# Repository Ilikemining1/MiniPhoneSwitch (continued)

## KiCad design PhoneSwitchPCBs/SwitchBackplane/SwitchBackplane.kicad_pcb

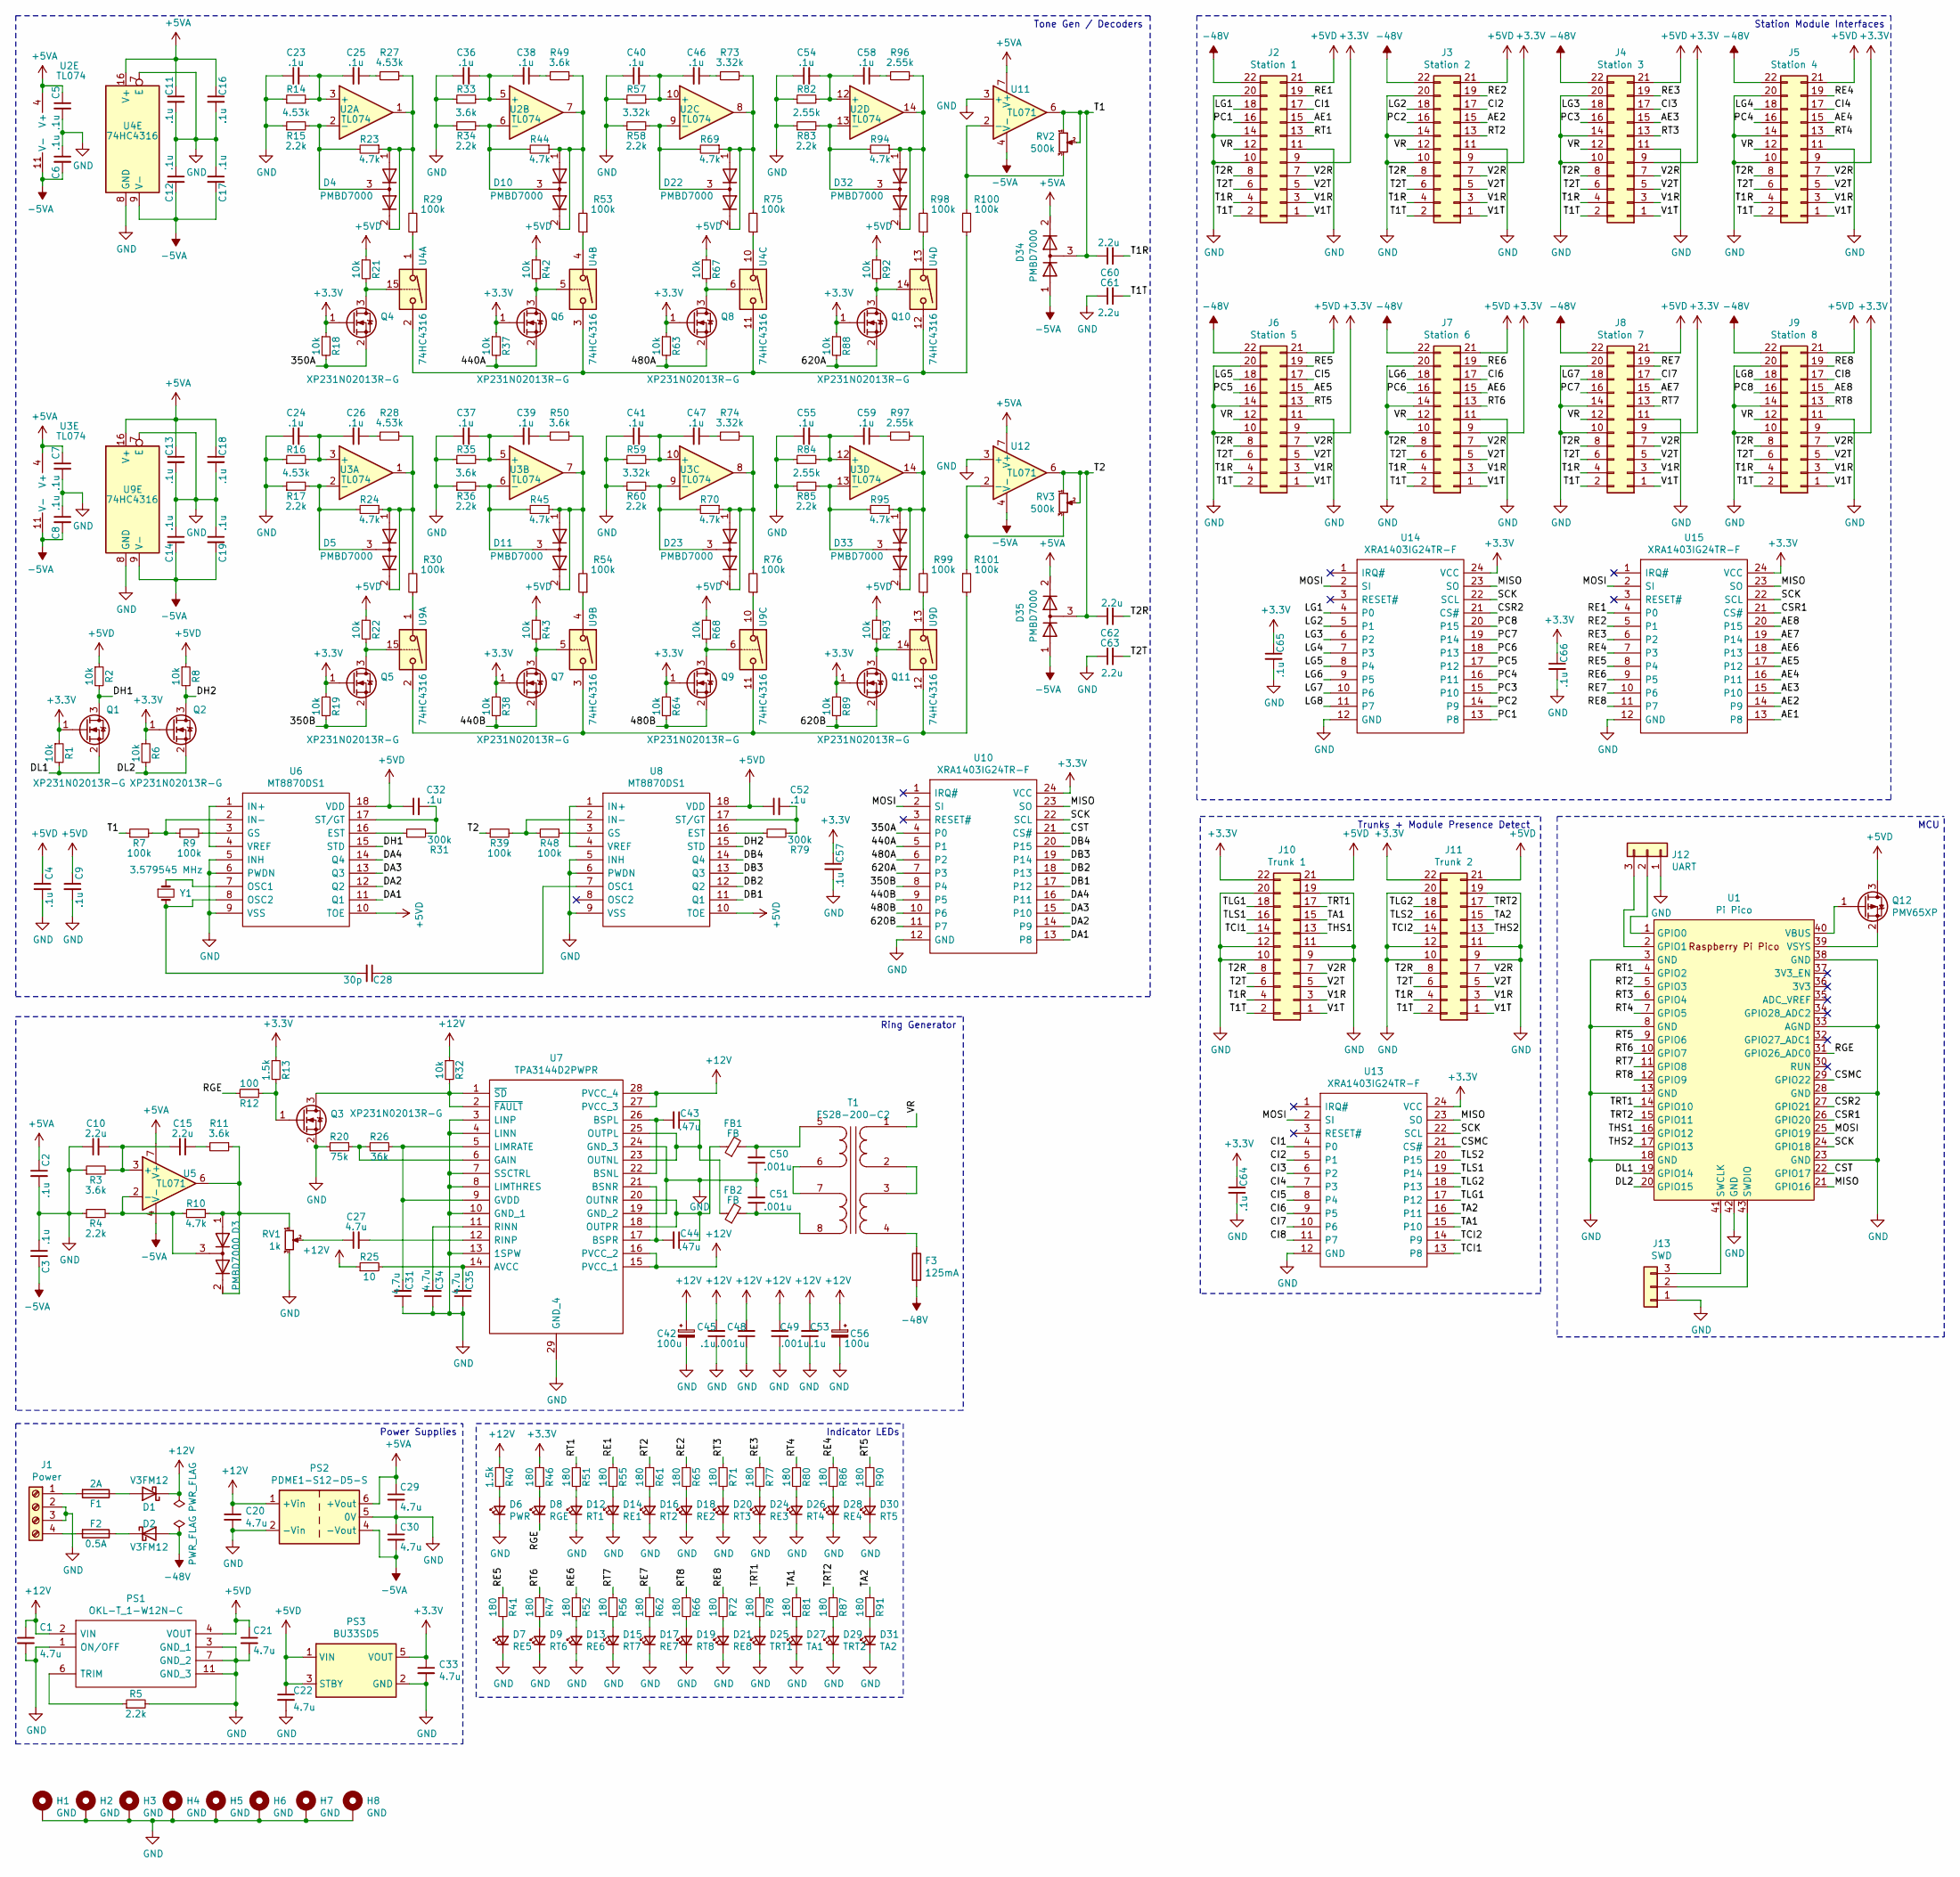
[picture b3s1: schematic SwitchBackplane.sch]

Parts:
C1, C20, C21, C22, C27, C29, C30, C31, C33, C34, C35: 4.7u; C_1206_3216Metric_Pad1.33x1.80mm_HandSolder
C2, C3, C4, C5, C6, C7, C8, C9, C11, C12, C13, C14, C16, C17, C18, C19, C32, C45, C52, C53, C57, C64, C65, C66: .1u; C_0603_1608Metric_Pad1.08x0.95mm_HandSolder
C10, C15: 2.2u; C_0805_2012Metric_Pad1.18x1.45mm_HandSolder
C23, C24, C25, C26, C36, C37, C38, C39, C40, C41, C46, C47, C54, C55, C58, C59: .1u; C_1206_3216Metric_Pad1.33x1.80mm_HandSolder
C28: 30p; C_0603_1608Metric_Pad1.08x0.95mm_HandSolder
C42, C56: 100u; CP_Radial_D6.3mm_P2.50mm
C43, C44: .47u; C_0805_2012Metric_Pad1.18x1.45mm_HandSolder
C48, C49, C50, C51: .001u; C_0603_1608Metric_Pad1.08x0.95mm_HandSolder
C60, C61, C62, C63: 2.2u; CP_Radial_D6.3mm_P2.50mm
D1, D2: V3FM12; D_SMF
D3, D4, D5, D10, D11, D22, D23, D32, D33, D34, D35: PMBD7000; SOT-23
D6: PWR; LED_0603_1608Metric_Pad1.05x0.95mm_HandSolder
D7: RE5; LED_0603_1608Metric_Pad1.05x0.95mm_HandSolder
D8: RGE; LED_0603_1608Metric_Pad1.05x0.95mm_HandSolder
D9: RT6; LED_0603_1608Metric_Pad1.05x0.95mm_HandSolder
D12: RT1; LED_0603_1608Metric_Pad1.05x0.95mm_HandSolder
D13: RE6; LED_0603_1608Metric_Pad1.05x0.95mm_HandSolder
D14: RE1; LED_0603_1608Metric_Pad1.05x0.95mm_HandSolder
D15: RT7; LED_0603_1608Metric_Pad1.05x0.95mm_HandSolder
D16: RT2; LED_0603_1608Metric_Pad1.05x0.95mm_HandSolder
D17: RE7; LED_0603_1608Metric_Pad1.05x0.95mm_HandSolder
D18: RE2; LED_0603_1608Metric_Pad1.05x0.95mm_HandSolder
D19: RT8; LED_0603_1608Metric_Pad1.05x0.95mm_HandSolder
D20: RT3; LED_0603_1608Metric_Pad1.05x0.95mm_HandSolder
D21: RE8; LED_0603_1608Metric_Pad1.05x0.95mm_HandSolder
D24: RE3; LED_0603_1608Metric_Pad1.05x0.95mm_HandSolder
D25: TRT1; LED_0603_1608Metric_Pad1.05x0.95mm_HandSolder
D26: RT4; LED_0603_1608Metric_Pad1.05x0.95mm_HandSolder
D27: TA1; LED_0603_1608Metric_Pad1.05x0.95mm_HandSolder
D28: RE4; LED_0603_1608Metric_Pad1.05x0.95mm_HandSolder
D29: TRT2; LED_0603_1608Metric_Pad1.05x0.95mm_HandSolder
D30: RT5; LED_0603_1608Metric_Pad1.05x0.95mm_HandSolder
D31: TA2; LED_0603_1608Metric_Pad1.05x0.95mm_HandSolder
F1: 2A; 00346605
F2: 0.5A; 00346605
F3: 125mA; 00346605
FB1, FB2: FB; NFZ2MSM101SN10B
H1, H2, H3, H4, H5, H6, H7, H8: GND; MountingHole_3.2mm_M3_Pad
J1: Power; VI0421550000G
J2: Station 1; PinSocket_2x11_P2.54mm_Vertical
J3: Station 2; PinSocket_2x11_P2.54mm_Vertical
J4: Station 3; PinSocket_2x11_P2.54mm_Vertical
J5: Station 4; PinSocket_2x11_P2.54mm_Vertical
J6: Station 5; PinSocket_2x11_P2.54mm_Vertical
J7: Station 6; PinSocket_2x11_P2.54mm_Vertical
J8: Station 7; PinSocket_2x11_P2.54mm_Vertical
J9: Station 8; PinSocket_2x11_P2.54mm_Vertical
J10: Trunk 1; PinSocket_2x11_P2.54mm_Vertical
J11: Trunk 2; PinSocket_2x11_P2.54mm_Vertical
J12: UART; PinHeader_1x03_P2.54mm_Vertical
J13: SWD; PinHeader_1x03_P2.54mm_Vertical
PS1: OKL-T_1-W12N-C; OKLT1W12NC; Mouser Part Number 580-OKL-T/1-W12N-C
PS2: PDME1-S12-D5-S; PDME1S12D5S
PS3: BU33SD5; SOT-23-5
Q1, Q2, Q3, Q4, Q5, Q6, Q7, Q8, Q9, Q10, Q11: XP231N02013R-G; SOT-323_SC-70_Handsoldering
Q12: PMV65XP; SOT-23
R1, R2, R6, R8, R18, R19, R21, R22, R32, R37, R38, R42, R43, R63, R64, R67, R68, R88, R89, R92, R93: 10k; R_0805_2012Metric_Pad1.20x1.40mm_HandSolder
R3, R11, R33, R35, R49, R50: 3.6k; R_0805_2012Metric_Pad1.20x1.40mm_HandSolder
R4, R5, R15, R17, R34, R36, R58, R60, R83, R85: 2.2k; R_0805_2012Metric_Pad1.20x1.40mm_HandSolder
R7, R9, R29, R30, R39, R48, R53, R54, R75, R76, R98, R99, R100, R101: 100k; R_0805_2012Metric_Pad1.20x1.40mm_HandSolder
R10, R23, R24, R44, R45, R69, R70, R94, R95: 4.7k; R_0805_2012Metric_Pad1.20x1.40mm_HandSolder
R12: 100; R_0805_2012Metric_Pad1.20x1.40mm_HandSolder
R13, R40: 1.5k; R_0805_2012Metric_Pad1.20x1.40mm_HandSolder
R14, R16, R27, R28: 4.53k; R_0805_2012Metric_Pad1.20x1.40mm_HandSolder
R20: 75k; R_0805_2012Metric_Pad1.20x1.40mm_HandSolder
R25: 10; R_0805_2012Metric_Pad1.20x1.40mm_HandSolder
R26: 36k; R_0805_2012Metric_Pad1.20x1.40mm_HandSolder
R31, R79: 300k; R_0805_2012Metric_Pad1.20x1.40mm_HandSolder
R41, R46, R47, R51, R52, R55, R56, R61, R62, R65, R66, R71, R72, R77, R78, R80, R81, R86, R87, R90, R91: 180; R_0603_1608Metric_Pad0.98x0.95mm_HandSolder
R57, R59, R73, R74: 3.32k; R_0805_2012Metric_Pad1.20x1.40mm_HandSolder
R82, R84, R96, R97: 2.55k; R_0805_2012Metric_Pad1.20x1.40mm_HandSolder
RV1: 1k; 35WR100KLFTR
RV2, RV3: 500k; TC33X-2_1
T1: FS28-200-C2; FS28200C2
U1: Pi Pico; RPi_Pico_SMD_TH
U2, U3: TL074; SOIC-14_3.9x8.7mm_P1.27mm
U4, U9: 74HC4316; SO-16_3.9x9.9mm_P1.27mm
U5, U11, U12: TL071; SOIC-8_3.9x4.9mm_P1.27mm
U6, U8: MT8870DS1; SOIC-18W_7.5x11.6mm_P1.27mm
U7: TPA3144D2PWPR; HTSSOP-28-1EP_4.4x9.7mm_P0.65mm_EP2.85x5.4mm_ThermalVias
U10, U13, U14, U15: XRA1403IG24TR-F; TSSOP-24_4.4x7.8mm_P0.65mm
Y1: 3.579545 MHz; Crystal_SMD_HC49-SD_HandSoldering

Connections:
+3V3: C33.1, C57.1, C64.1, C65.1, C66.1, J2.9, J3.9, J4.9, J5.9, J6.9, J7.9, J8.9, J9.9, J10.22, J11.22, PS3.5 (VOUT), Q1.1 (G), Q2.1 (G), Q4.1 (G), Q5.1 (G), Q6.1 (G), Q7.1 (G), Q8.1 (G), Q9.1 (G), Q10.1 (G), Q11.1 (G), R1.1, R6.1, R13.1, R18.1, R19.1, R37.1, R38.1, R46.1, R63.1, R64.1, R88.1, R89.1, U10.24 (VCC), U13.24 (VCC), U14.24 (VCC), U15.24 (VCC)
+5VA: C2.1, C5.1, C7.1, C11.1, C13.1, C16.1, C18.1, C29.1, D34.2 (K2), D35.2 (K2), PS2.6 (+Vout), U2.4 (V+), U3.4 (V+), U4.16 (V+), U5.7 (V+), U9.16 (V+), U11.7 (V+), U12.7 (V+)
+5VD: C4.1, C9.1, C21.1, C22.1, C32.1, C52.1, J2.21, J3.21, J4.21, J5.21, J6.21, J7.21, J8.21, J9.21, J10.21, J11.21, PS1.4 (VOUT), PS3.1 (VIN), PS3.3 (STBY), Q12.3 (D), R2.1, R8.1, R21.1, R22.1, R42.1, R43.1, R67.1, R68.1, R92.1, R93.1, U6.10 (TOE), U6.18 (VDD), U8.10 (TOE), U8.18 (VDD)
+12V: C1.1, C20.1, C42.1, C45.2, C48.2, C49.2, C53.2, C56.1, D1.1 (K), PS1.2 (VIN), PS2.1 (+Vin), R25.1, R32.1, R40.1, U7.15 (PVCC_1), U7.16 (PVCC_2), U7.27 (PVCC_3), U7.28 (PVCC_4)
-5VA: C3.2, C6.2, C8.2, C12.2, C14.2, C17.2, C19.2, C30.2, D34.1 (A1), D35.1 (A1), PS2.4 (-Vout), U2.11 (V-), U3.11 (V-), U4.9 (V-), U5.4 (V-), U9.9 (V-), U11.4 (V-), U12.4 (V-)
-48V: D2.2 (A), F3.2, J2.22, J3.22, J4.22, J5.22, J6.22, J7.22, J8.22, J9.22
/350A: Q4.2 (S), R18.2, U10.4 (P0)
/350B: Q5.2 (S), R19.2, U10.8 (P4)
/440A: Q6.2 (S), R37.2, U10.5 (P1)
/440B: Q7.2 (S), R38.2, U10.9 (P5)
/480A: Q8.2 (S), R63.2, U10.6 (P2)
/480B: Q9.2 (S), R64.2, U10.10 (P6)
/620A: Q10.2 (S), R88.2, U10.7 (P3)
/620B: Q11.2 (S), R89.2, U10.11 (P7)
/AE1: J2.15, U15.13 (P8)
/AE2: J3.15, U15.14 (P9)
/AE3: J4.15, U15.15 (P10)
/AE4: J5.15, U15.16 (P11)
/AE5: J6.15, U15.17 (P12)
/AE6: J7.15, U15.18 (P13)
/AE7: J8.15, U15.19 (P14)
/AE8: J9.15, U15.20 (P15)
/CI1: J2.17, U13.4 (P0)
/CI2: J3.17, U13.5 (P1)
/CI3: J4.17, U13.6 (P2)
/CI4: J5.17, U13.7 (P3)
/CI5: J6.17, U13.8 (P4)
/CI6: J7.17, U13.9 (P5)
/CI7: J8.17, U13.10 (P6)
/CI8: J9.17, U13.11 (P7)
/CSMC: U1.29 (GPIO22), U13.21 (CS#)
/CSR1: U1.26 (GPIO20), U15.21 (CS#)
/CSR2: U1.27 (GPIO21), U14.21 (CS#)
/CST: U1.22 (GPIO17), U10.21 (CS#)
/DA1: U6.11 (Q1), U10.13 (P8)
/DA2: U6.12 (Q2), U10.14 (P9)
/DA3: U6.13 (Q3), U10.15 (P10)
/DA4: U6.14 (Q4), U10.16 (P11)
/DB1: U8.11 (Q1), U10.17 (P12)
/DB2: U8.12 (Q2), U10.18 (P13)
/DB3: U8.13 (Q3), U10.19 (P14)
/DB4: U8.14 (Q4), U10.20 (P15)
/DH1: Q1.3 (D), R2.2, U6.15 (STD)
/DH2: Q2.3 (D), R8.2, U8.15 (STD)
/DL1: Q1.2 (S), R1.2, U1.19 (GPIO14)
/DL2: Q2.2 (S), R6.2, U1.20 (GPIO15)
/LG1: J2.18, U14.4 (P0)
/LG2: J3.18, U14.5 (P1)
/LG3: J4.18, U14.6 (P2)
/LG4: J5.18, U14.7 (P3)
/LG5: J6.18, U14.8 (P4)
/LG6: J7.18, U14.9 (P5)
/LG7: J8.18, U14.10 (P6)
/LG8: J9.18, U14.11 (P7)
/MISO: U1.21 (GPIO16), U10.23 (SO), U13.23 (SO), U14.23 (SO), U15.23 (SO)
/MOSI: U1.25 (GPIO19), U10.2 (SI), U13.2 (SI), U14.2 (SI), U15.2 (SI)
/PC1: J2.16, U14.13 (P8)
/PC2: J3.16, U14.14 (P9)
/PC3: J4.16, U14.15 (P10)
/PC4: J5.16, U14.16 (P11)
/PC5: J6.16, U14.17 (P12)
/PC6: J7.16, U14.18 (P13)
/PC7: J8.16, U14.19 (P14)
/PC8: J9.16, U14.20 (P15)
/RE1: J2.19, R55.1, U15.4 (P0)
/RE2: J3.19, R65.1, U15.5 (P1)
/RE3: J4.19, R77.1, U15.6 (P2)
/RE4: J5.19, R86.1, U15.7 (P3)
/RE5: J6.19, R41.1, U15.8 (P4)
/RE6: J7.19, R52.1, U15.9 (P5)
/RE7: J8.19, R62.1, U15.10 (P6)
/RE8: J9.19, R72.1, U15.11 (P7)
/RGE: D8.1 (K), R12.2, U1.31 (GPIO26_ADC0)
/RT1: J2.13, R51.1, U1.4 (GPIO2)
/RT2: J3.13, R61.1, U1.5 (GPIO3)
/RT3: J4.13, R71.1, U1.6 (GPIO4)
/RT4: J5.13, R80.1, U1.7 (GPIO5)
/RT5: J6.13, R90.1, U1.9 (GPIO6)
/RT6: J7.13, R47.1, U1.10 (GPIO7)
/RT7: J8.13, R56.1, U1.11 (GPIO8)
/RT8: J9.13, R66.1, U1.12 (GPIO9)
/SCK: U1.24 (GPIO18), U10.22 (SCL), U13.22 (SCL), U14.22 (SCL), U15.22 (SCL)
/T1: C60.1, D34.3 (K1A2), R7.1, RV2.1, RV2.2, U11.6
/T1R: C60.2, J2.4, J3.4, J4.4, J5.4, J6.4, J7.4, J8.4, J9.4, J10.4, J11.4
/T1T: C61.2, J2.2, J3.2, J4.2, J5.2, J6.2, J7.2, J8.2, J9.2, J10.2, J11.2
/T2: C62.1, D35.3 (K1A2), R39.1, RV3.1, RV3.2, U12.6
/T2R: C62.2, J2.8, J3.8, J4.8, J5.8, J6.8, J7.8, J8.8, J9.8, J10.8, J11.8
/T2T: C63.2, J2.6, J3.6, J4.6, J5.6, J6.6, J7.6, J8.6, J9.6, J10.6, J11.6
/TA1: J10.15, R81.1, U13.15 (P10)
/TA2: J11.15, R91.1, U13.16 (P11)
/TCI1: J10.14, U13.13 (P8)
/TCI2: J11.14, U13.14 (P9)
/THS1: J10.13, U1.16 (GPIO12)
/THS2: J11.13, U1.17 (GPIO13)
/TLG1: J10.18, U13.17 (P12)
/TLG2: J11.18, U13.18 (P13)
/TLS1: J10.16, U13.19 (P14)
/TLS2: J11.16, U13.20 (P15)
/TRT1: J10.17, R78.1, U1.14 (GPIO10)
/TRT2: J11.17, R87.1, U1.15 (GPIO11)
/V1R: J2.3, J3.3, J4.3, J5.3, J6.3, J7.3, J8.3, J9.3, J10.3, J11.3
/V1T: J2.1, J3.1, J4.1, J5.1, J6.1, J7.1, J8.1, J9.1, J10.1, J11.1
/V2R: J2.7, J3.7, J4.7, J5.7, J6.7, J7.7, J8.7, J9.7, J10.7, J11.7
/V2T: J2.5, J3.5, J4.5, J5.5, J6.5, J7.5, J8.5, J9.5, J10.5, J11.5
/VR: J2.12, J3.12, J4.12, J5.12, J6.12, J7.12, J8.12, J9.12, T1.1 (PA)
GND: C1.2, C2.2, C3.1, C4.2, C5.2, C6.1, C7.2, C8.1, C9.2, C10.1, C11.2, C12.1, C13.2, C14.1, C16.2, C17.1, C18.2, C19.1, C20.2, C21.2, C22.2, C23.1, C24.1, C29.2, C30.1, C31.1, C33.2, C34.1, C35.1, C36.1, C37.1, C40.1, C41.1, C42.2, C45.1, C48.1, C49.1, C50.1, C51.2, C53.1, C54.1, C55.1, C56.2, C57.2, C61.1, C63.1, C64.2, C65.2, C66.2, D6.1 (K), D7.1 (K), D9.1 (K), D12.1 (K), D13.1 (K), D14.1 (K), D15.1 (K), D16.1 (K), D17.1 (K), D18.1 (K), D19.1 (K), D20.1 (K), D21.1 (K), D24.1 (K), D25.1 (K), D26.1 (K), D27.1 (K), D28.1 (K), D29.1 (K), D30.1 (K), D31.1 (K), H1.1, H2.1, H3.1, H4.1, H5.1, H6.1, H7.1, H8.1, J1.2, J1.3, J2.10, J2.11, J2.14, J2.20, J3.10, J3.11, J3.14, J3.20, J4.10, J4.11, J4.14, J4.20, J5.10, J5.11, J5.14, J5.20, J6.10, J6.11, J6.14, J6.20, J7.10, J7.11, J7.14, J7.20, J8.10, J8.11, J8.14, J8.20, J9.10, J9.11, J9.14, J9.20, J10.9, J10.10, J10.11, J10.12, J10.19, J10.20, J11.9, J11.10, J11.11, J11.12, J11.19, J11.20, J12.1, J13.1, PS1.1 (ON/OFF), PS1.3 (GND_1), PS1.7 (GND_2), PS1.11 (GND_3), PS2.2 (-Vin), PS2.5 (0V), PS3.2 (GND), Q3.2 (S), R3.1, R4.1, R5.2, R14.1, R15.1, R16.1, R17.1, R20.1, R33.1, R34.1, R35.1, R36.1, R57.1, R58.1, R59.1, R60.1, R82.1, R83.1, R84.1, R85.1, RV1.3, U1.3 (GND), U1.8 (GND), U1.13 (GND), U1.18 (GND), U1.23 (GND), U1.28 (GND), U1.33 (AGND), U1.38 (GND), U1.42 (GND), U4.7 (E), U4.8 (GND), U6.5 (INH), U6.6 (PWDN), U6.9 (VSS), U7.3 (LINP), U7.4 (LINN), U7.7 (SSCTRL), U7.8 (LIMTHRES), U7.10 (GND_1), U7.13 (1SPW), U7.19 (GND_2), U7.24 (GND_3), U7.29 (GND_4), U8.5 (INH), U8.6 (PWDN), U8.9 (VSS), U9.7 (E), U9.8 (GND), U10.12 (GND), U11.3 (+), U12.3 (+), U13.12 (GND), U14.12 (GND), U15.12 (GND)
unnamed: C10.2, C15.2, R3.2, U5.3 (+)
unnamed: C15.1, R11.2
unnamed: C23.2, C25.2, R14.2, U2.3 (+)
unnamed: C24.2, C26.2, R16.2, U3.3 (+)
unnamed: C25.1, R27.2
unnamed: C26.1, R28.2
unnamed: C27.1, RV1.2
unnamed: C27.2, U7.12 (RINP)
unnamed: C28.1, U8.7 (OSC1)
unnamed: C28.2, U6.8 (OSC2), Y1.2
unnamed: C31.2, R26.2, U7.5 (LIMRATE), U7.9 (GVDD)
unnamed: C32.2, R31.2, U6.17 (ST/GT)
unnamed: C34.2, U7.11 (RINN)
unnamed: C35.2, R25.2, U7.14 (AVCC)
unnamed: C36.2, C38.2, R33.2, U2.5 (+)
unnamed: C37.2, C39.2, R35.2, U3.5 (+)
unnamed: C38.1, R49.2
unnamed: C39.1, R50.2
unnamed: C40.2, C46.2, R57.2, U2.10 (+)
unnamed: C41.2, C47.2, R59.2, U3.10 (+)
unnamed: C43.1, FB2.1, U7.23 (OUTNL), U7.25 (OUTPL)
unnamed: C43.2, U7.22 (BSNL), U7.26 (BSPL)
unnamed: C44.1, FB1.1, U7.18 (OUTPR), U7.20 (OUTNR)
unnamed: C44.2, U7.17 (BSPR), U7.21 (BSNR)
unnamed: C46.1, R73.2
unnamed: C47.1, R74.2
unnamed: C50.2, FB1.2, T1.5 (SA)
unnamed: C51.1, FB2.2, T1.8 (SB)
unnamed: C52.2, R79.2, U8.17 (ST/GT)
unnamed: C54.2, C58.2, R82.2, U2.12 (+)
unnamed: C55.2, C59.2, R84.2, U3.12 (+)
unnamed: C58.1, R96.2
unnamed: C59.1, R97.2
unnamed: D1.2 (A), F1.1
unnamed: D2.1 (K), F2.1
unnamed: D3.1 (A1), D3.2 (K2), R10.1, R11.1, RV1.1, U5.6
unnamed: D3.3 (K1A2), R4.2, R10.2, U5.2 (-)
unnamed: D4.1 (A1), D4.2 (K2), R23.1, R27.1, R29.2, U2.1
unnamed: D4.3 (K1A2), R15.2, R23.2, U2.2 (-)
unnamed: D5.1 (A1), D5.2 (K2), R24.1, R28.1, R30.2, U3.1
unnamed: D5.3 (K1A2), R17.2, R24.2, U3.2 (-)
unnamed: D6.2 (A), R40.2
unnamed: D7.2 (A), R41.2
unnamed: D8.2 (A), R46.2
unnamed: D9.2 (A), R47.2
unnamed: D10.1 (A1), D10.2 (K2), R44.1, R49.1, R53.2, U2.7
unnamed: D10.3 (K1A2), R34.2, R44.2, U2.6 (-)
unnamed: D11.1 (A1), D11.2 (K2), R45.1, R50.1, R54.2, U3.7
unnamed: D11.3 (K1A2), R36.2, R45.2, U3.6 (-)
unnamed: D12.2 (A), R51.2
unnamed: D13.2 (A), R52.2
unnamed: D14.2 (A), R55.2
unnamed: D15.2 (A), R56.2
unnamed: D16.2 (A), R61.2
unnamed: D17.2 (A), R62.2
unnamed: D18.2 (A), R65.2
unnamed: D19.2 (A), R66.2
unnamed: D20.2 (A), R71.2
unnamed: D21.2 (A), R72.2
unnamed: D22.1 (A1), D22.2 (K2), R69.1, R73.1, R75.2, U2.8
unnamed: D22.3 (K1A2), R58.2, R69.2, U2.9 (-)
unnamed: D23.1 (A1), D23.2 (K2), R70.1, R74.1, R76.2, U3.8
unnamed: D23.3 (K1A2), R60.2, R70.2, U3.9 (-)
unnamed: D24.2 (A), R77.2
unnamed: D25.2 (A), R78.2
unnamed: D26.2 (A), R80.2
unnamed: D27.2 (A), R81.2
unnamed: D28.2 (A), R86.2
unnamed: D29.2 (A), R87.2
unnamed: D30.2 (A), R90.2
unnamed: D31.2 (A), R91.2
unnamed: D32.1 (A1), D32.2 (K2), R94.1, R96.1, R98.2, U2.14
unnamed: D32.3 (K1A2), R83.2, R94.2, U2.13 (-)
unnamed: D33.1 (A1), D33.2 (K2), R95.1, R97.1, R99.2, U3.14
unnamed: D33.3 (K1A2), R85.2, R95.2, U3.13 (-)
unnamed: F1.2, J1.1
unnamed: F2.2, J1.4
unnamed: F3.1, T1.4 (PB)
unnamed: J12.2, U1.1 (GPIO0)
unnamed: J12.3, U1.2 (GPIO1)
unnamed: J13.2, U1.43 (SWDIO)
unnamed: J13.3, U1.41 (SWCLK)
unnamed: PS1.6 (TRIM), R5.1
unnamed: Q3.1 (G), R12.1, R13.2
unnamed: Q3.3 (D), R32.2, U7.1 (~SD), U7.2 (~FAULT)
unnamed: Q4.3 (D), R21.2, U4.15
unnamed: Q5.3 (D), R22.2, U9.15
unnamed: Q6.3 (D), R42.2, U4.5
unnamed: Q7.3 (D), R43.2, U9.5
unnamed: Q8.3 (D), R67.2, U4.6
unnamed: Q9.3 (D), R68.2, U9.6
unnamed: Q10.3 (D), R92.2, U4.14
unnamed: Q11.3 (D), R93.2, U9.14
unnamed: Q12.1 (G), U1.40 (VBUS)
unnamed: Q12.2 (S), U1.39 (VSYS)
unnamed: R7.2, R9.1, U6.2 (IN-)
unnamed: R9.2, U6.3 (GS)
unnamed: R20.2, R26.1, U7.6 (GAIN)
unnamed: R29.1, U4.1
unnamed: R30.1, U9.1
unnamed: R31.1, U6.16 (EST)
unnamed: R39.2, R48.1, U8.2 (IN-)
unnamed: R48.2, U8.3 (GS)
unnamed: R53.1, U4.4
unnamed: R54.1, U9.4
unnamed: R75.1, U4.10
unnamed: R76.1, U9.10
unnamed: R79.1, U8.16 (EST)
unnamed: R98.1, U4.13
unnamed: R99.1, U9.13
unnamed: R100.1, RV2.3, U11.2 (-)
unnamed: R100.2, U4.2, U4.3, U4.11, U4.12
unnamed: R101.1, RV3.3, U12.2 (-)
unnamed: R101.2, U9.2, U9.3, U9.11, U9.12
unnamed: T1.2 (PA), T1.3 (PB)
unnamed: T1.6 (SA), T1.7 (SB)
unnamed: U6.1 (IN+), U6.4 (VREF)
unnamed: U6.7 (OSC1), Y1.1
unnamed: U8.1 (IN+), U8.4 (VREF)

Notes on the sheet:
Tone Gen / Decoders
Station Module Interfaces
Power Supplies
Ring Generator
Indicator LEDs
Trunks + Module Presence Detect
MCU

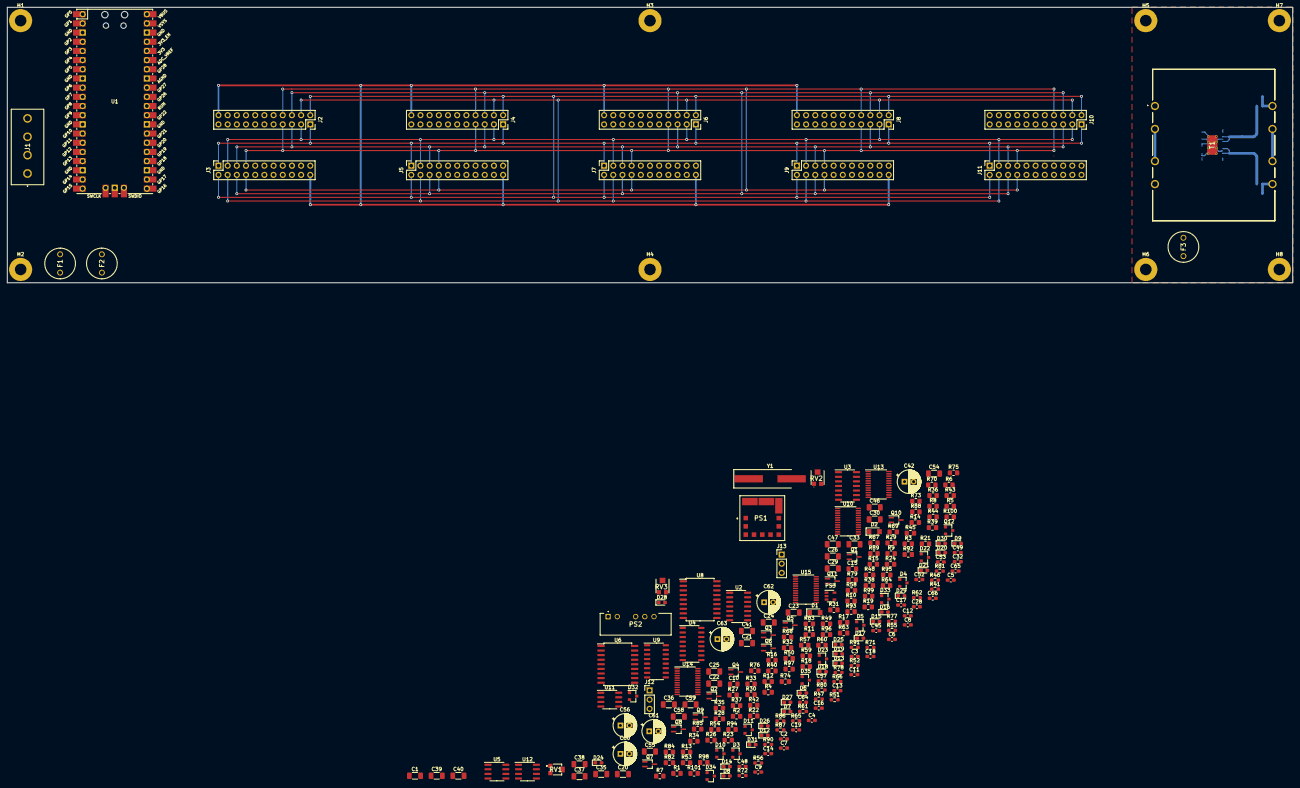
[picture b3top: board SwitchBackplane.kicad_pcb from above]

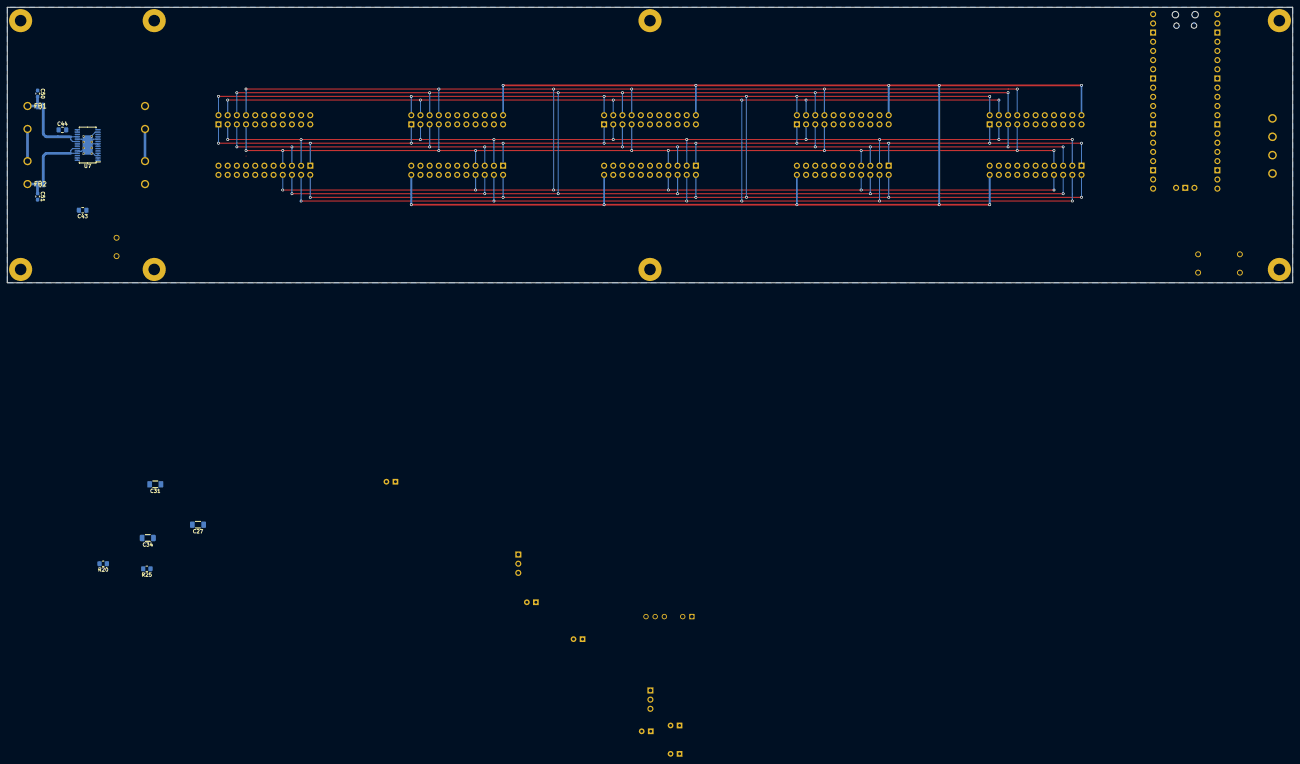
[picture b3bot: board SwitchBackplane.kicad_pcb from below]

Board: 2 copper layers, 355.6 x 76.2 mm, 263 parts (12 on the bottom side), 225 nets.

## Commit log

2021-07-19 Initial commit, start using version control
    Initial commit on the MiniPhoneSwitch project, including current schematics, notes, and simulation designs / models.
2021-07-20 Update notes based on changing plans, minor changes to schematics and sim files
2021-07-20 Added diagram of switch
    Added the first revision of the design diagram of my switch.
2021-07-20 Add PNG of Diagram
2021-07-21 Fixed typo. "grunk" is now "trunk"
2021-07-21 Update design notes with info on microcontroller pin requirements
2021-07-21 Add note on IO Expanders
2021-07-22 Updated schematics and notes
    Changed pin count for using analog switch bypass of ring cut filter, worked more on schematics, including deciding to put routing on line modules.
2021-07-22 Update notes and progress on schematics
    Further work on station card schematics, changed some things in notes.
2021-07-22 Continued work on schematic
2021-07-23 Continue work on schematic and add more notes
2021-07-24 Progress on schematic, switch to using software filtering
    Clean up notes regarding only needing a single Schmitt trigger for software-based filtering of ring trip. Remove the unneeded switch IC from notes as well as the schematic, and remove the filter.
2021-07-24 Update and clarify notes
2021-07-24 Update notes, change schematic to use 3.3 volt IO in addition to more progress
2021-07-24 Add note about other IO Expander
2021-07-24 Finalize non-interchangeable station/trunk modules, mostly finish schematic
2021-07-24 Minor schematic touchups, removed unneeded project file, add PDF schematic
2021-07-24 Added current limit functionality, simplified voice/tone relay logic
2021-07-24 Fixed reversed PNP polarity
2021-07-25 Update Notes, create custom footprint for RJ11 connector, associate footprints, fix cap types
2021-07-25 Finished footprint associations
2021-07-25 Use ugly hack to add the extra emitter pins on the power transistors, generate netlist
2021-07-25 Start initial PCB layout, fix some small mistakes in schematic
2021-07-25 Update schematic PDF
2021-07-25 More progress to PCB Layout
2021-07-26 Mostly finish trace routing.
2021-07-26 tweaked detect resistor to pulldown, finished routing all tracks!
2021-07-26 Remove extra cap from schematic, finish up PCB design
2021-07-26 Minor tweaks before PCB attempt 2
2021-07-26 Rename OLD PCB layout, remove unneeded netlist, update schematic PDF
2021-07-26 Start NEW more carefully laid out PCB. Completed gyrator sections.
2021-07-26 More progress, added two extra mounting holes
2021-07-27 Tweaked schematic to make routing easier
2021-07-27 Finished routing tracks
2021-07-27 Finalize PCB, move around silkscreen markings
2021-07-27 Fixed a minor issue with the silkscreen
2021-07-27 Generate initial Gerbers
2021-08-04 Updated gerbers, added zip, added relay 3d model
2021-08-19 Delete PhoneInterfaceOLD.kicad_pcb
    Remove old PCB design
2021-08-23 Started on Switch Backplane schematic, updated notes on tone generation and power supplies
2021-08-23 Continue work on backplane schematic
2021-08-23 Added simulation of tone generators, updated backplane schematic
2021-08-23 Updated notes, regenerated audio, updated spice sim to use proper RC values
2021-08-25 Cleaned up and clarified notes
2021-08-25 Continued work on backplane schematic
2021-08-26 Add station interface ports, initial power supply design
2021-08-26 Update notes on ring generator and continued schematic work
2021-08-27 Continued backplane schematic work
2021-08-27 Added ring generator oscillator spice sim and continued work on schematics
2021-08-27 Clean up git structure, move interface designs into their own folder
    Clean up the mess that's been building up so far.
2021-08-27 Update outdated info in the Design Notes
2021-08-27 Continue work on the backplane schematic and add Pi Pico footprint files
2021-08-27 Fix library table entries
2021-08-28 Update notes and progress more on schematic
2021-08-29 Tweak notes
2021-08-29 Continue work on schematic
2021-08-30 Clarify pin counts and fix notes error, continue work on schematic
2021-08-31 More work on schematics
2021-08-31 Further work on schematic, rearranged some things on IO expander ICs
2021-09-01 Start to finish up schematic, add PDF of current schematic revision
2021-09-01 Fixed a few small issues, annotated schematic, cleaned up annotations, fixed issue with switch ICs
    The annotations were a mess, cleaned them all up. Also modified some components so the ERC would stop complaining. Fixed the issue with forgetting to connect switch IC enable, and finally made all th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
2021-09-01 Associate footprints with parts, other tweaks
2021-09-01 Tweaks to schematic, associate all footprints
2021-09-01 Update footprint libraries, fixed broken footprint association
2021-09-01 Initial PCB commit
2021-09-01 Add mounting holes to schematic
2021-09-02 More work on PCB
2021-09-03 Adjusted PCB Dimensions
2021-09-03 Align module connectors
2021-09-03 Added more mounting holes for transformer
2021-09-04 more PCB chaos
2021-09-05 Connect voice and tone pins
2021-09-05 More track routing
2022-02-13 Adapted and updated schematics and PCB design.
    Converted schematics and board layouts to new file, as well as move design from one backplane to multiple modules.
2022-02-13 Remove old format libs
2022-02-13 Started creating new tone production/decoder board
2022-02-15 More work on Tone Gen/Decoder schematic
2022-02-16 Finish? Tone Generator / Decoder Schematic
2022-02-26 Finished schematic, started work on PCB design.
2022-04-02 More work on PCB Layout
2022-04-02 Mostly Finished Tone Gen Layout
2022-04-02 Connect signals to switch IC
2022-04-03 Cleaned up tone generator placement
2022-04-03 Redoing layout
    Redoing layout to fix the issues related to the in/mm switch at some point and me not noticing.
2022-04-03 Laid out tone gens again
2022-04-03 Power traces, among other things
2022-04-03 More layout
2022-04-04 Finish routing (for the first time)
    Okay, unrouted nets says 0. However, this could probably use some cleanup.
2022-04-09 Arrange Silkscreen Values
2022-04-09 Finishing touches on PCB design
2022-04-09 Generate Gerbers
2022-04-09 Added JLC text for number placement
2022-04-10 Initial commit of Station Module Backplanes
